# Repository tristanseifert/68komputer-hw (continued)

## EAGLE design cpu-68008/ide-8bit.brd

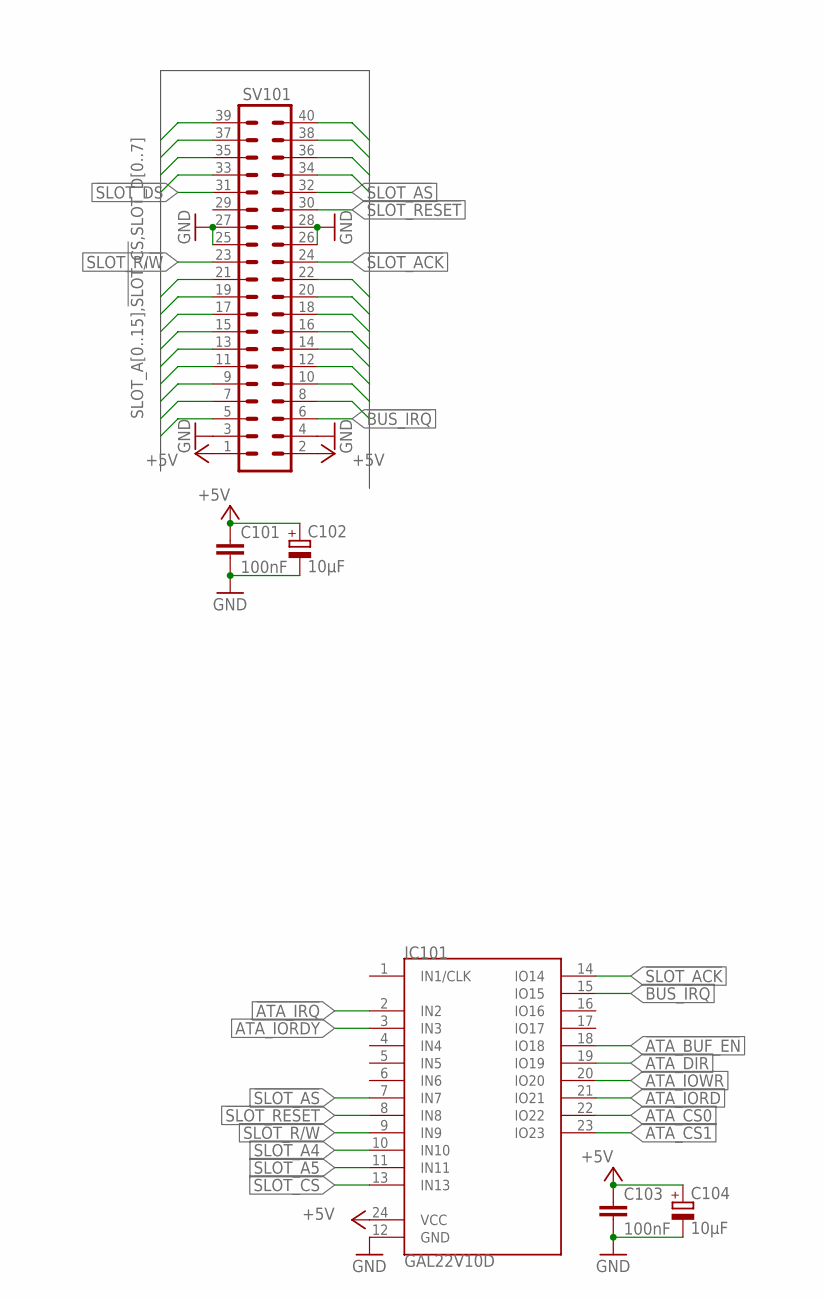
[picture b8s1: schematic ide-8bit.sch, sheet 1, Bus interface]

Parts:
C101, C103: 100nF; C0805; MOUSER 710-885012207072
C102, C104: 10µF; SMC_B; MOUSER 581-TAJB106K020RNJV
IC101: GAL22V10D; DIL24S; MOUSER_SOCKET 575-11044324
SV101: MA20-2W

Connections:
!ATA_BUF_EN: IC101.18 (IO18); also elsewhere on the board
!ATA_CS0: IC101.22 (IO22); also elsewhere on the board
!ATA_CS1: IC101.23 (IO23); also elsewhere on the board
!ATA_IRQ: IC101.2 (IN2); also elsewhere on the board
!BUS_IRQ: IC101.15 (IO15), SV101.6
!SLOT_ACK: IC101.14 (IO14), SV101.24
!SLOT_AS: IC101.7 (IN7), SV101.32
!SLOT_CS: IC101.13 (IN13), SV101.5
!SLOT_DS: SV101.31
!SLOT_RESET: IC101.8 (IN8), SV101.30
+5V: C101.1, C102.+, C103.1, C104.+, IC101.24 (VCC), SV101.1, SV101.2; also elsewhere on the board
ATA_DIR: IC101.19 (IO19); also elsewhere on the board
ATA_IORD: IC101.21 (IO21); also elsewhere on the board
ATA_IORDY: IC101.3 (IN3); also elsewhere on the board
ATA_IOWR: IC101.20 (IO20); also elsewhere on the board
GND: C101.2, C102.-, C103.2, C104.-, IC101.12 (GND), SV101.3, SV101.4, SV101.25, SV101.26, SV101.27, SV101.28; also elsewhere on the board
SLOT_A0: SV101.12; also elsewhere on the board
SLOT_A1: SV101.10; also elsewhere on the board
SLOT_A2: SV101.8; also elsewhere on the board
SLOT_A3: SV101.7
SLOT_A4: IC101.10 (IN10), SV101.9
SLOT_A5: IC101.11 (IN11), SV101.11
SLOT_A6: SV101.14
SLOT_A7: SV101.13
SLOT_A8: SV101.16
SLOT_A9: SV101.15
SLOT_A10: SV101.18
SLOT_A11: SV101.17
SLOT_A12: SV101.20
SLOT_A13: SV101.19
SLOT_A14: SV101.22
SLOT_A15: SV101.21
SLOT_D0: SV101.35; also elsewhere on the board
SLOT_D1: SV101.37; also elsewhere on the board
SLOT_D2: SV101.39; also elsewhere on the board
SLOT_D3: SV101.40; also elsewhere on the board
SLOT_D4: SV101.38; also elsewhere on the board
SLOT_D5: SV101.36; also elsewhere on the board
SLOT_D6: SV101.34; also elsewhere on the board
SLOT_D7: SV101.33; also elsewhere on the board
SLOT_R/!W!: IC101.9 (IN9), SV101.23

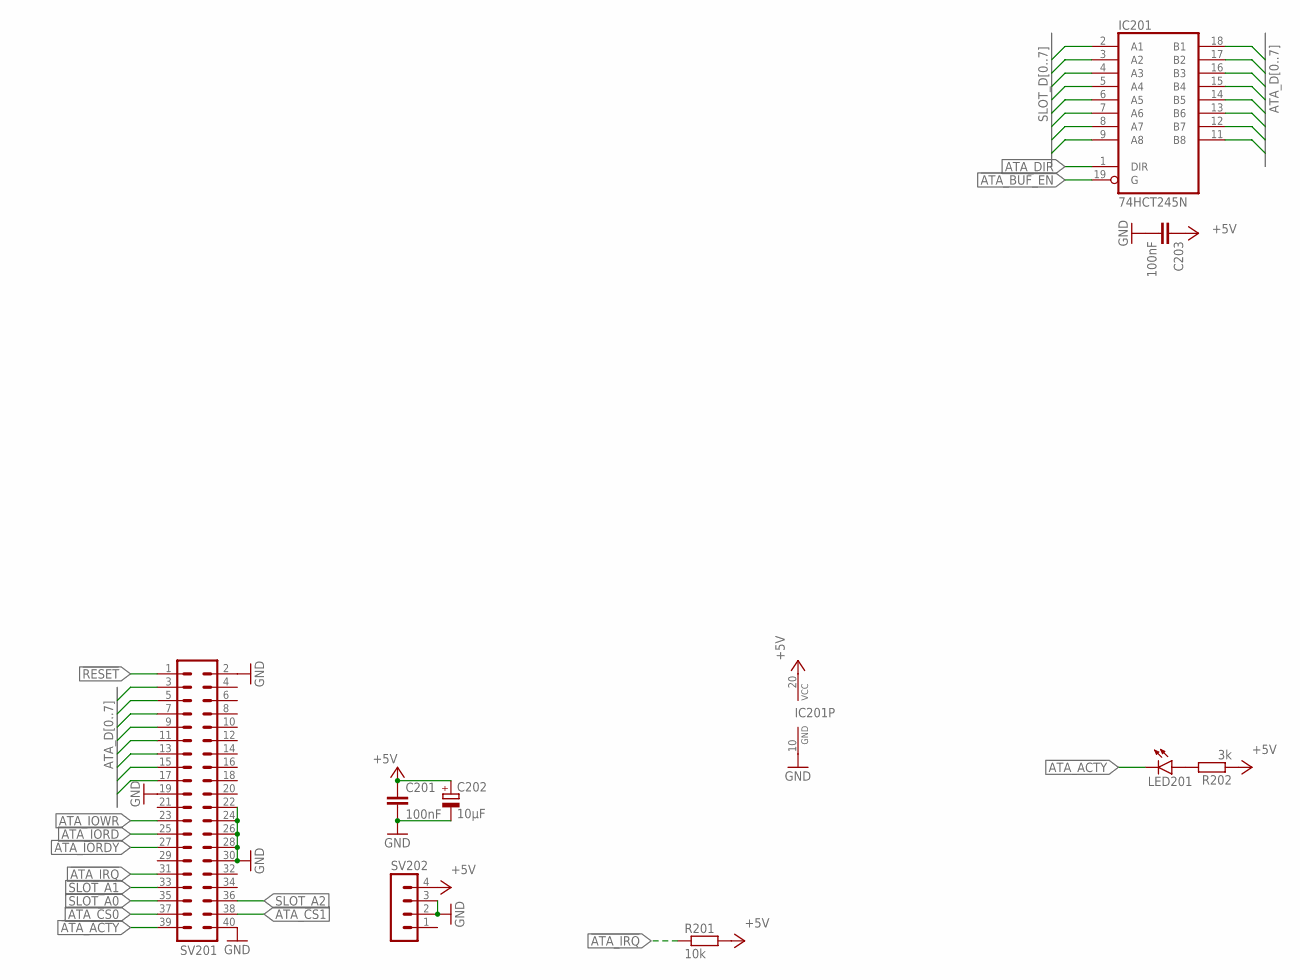
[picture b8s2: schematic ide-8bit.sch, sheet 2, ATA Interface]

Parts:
C201, C203: 100nF; C0805; MOUSER 710-885012207072
C202: 10µF; SMC_B; MOUSER 581-TAJB106K020RNJV
IC201: 74HCT245N; DIL20; MOUSER 595-SN74HCT245N
LED201: LEDCHIPLED_1206; CHIPLED_1206; MOUSER 710-156120VS75300
R201: 10k; R2012; MOUSER 652-CR0805FX-1002ELF
R202: 3k; R2012; MOUSER 652-CR0805JW-302ELF
SV201: ML40L
SV202: MA04-1

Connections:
!ATA_ACTY: LED201.C, SV201.39
!ATA_BUF_EN: IC201.19 (G); also elsewhere on the board
!ATA_CS0: SV201.37; also elsewhere on the board
!ATA_CS1: SV201.38; also elsewhere on the board
!ATA_IRQ: R201.1, SV201.31; also elsewhere on the board
!RESET: SV201.1
+5V: C201.1, C202.+, C203.1, IC201.20 (VCC), R201.2, R202.1, SV202.4; also elsewhere on the board
ATA_D0: IC201.18 (B1), SV201.17
ATA_D1: IC201.17 (B2), SV201.15
ATA_D2: IC201.16 (B3), SV201.13
ATA_D3: IC201.15 (B4), SV201.11
ATA_D4: IC201.14 (B5), SV201.9
ATA_D5: IC201.13 (B6), SV201.7
ATA_D6: IC201.12 (B7), SV201.5
ATA_D7: IC201.11 (B8), SV201.3
ATA_DIR: IC201.1 (DIR); also elsewhere on the board
ATA_IORD: SV201.25; also elsewhere on the board
ATA_IORDY: SV201.27; also elsewhere on the board
ATA_IOWR: SV201.23; also elsewhere on the board
GND: C201.2, C202.-, C203.2, IC201.10 (GND), SV201.2, SV201.19, SV201.22, SV201.24, SV201.26, SV201.28, SV201.30, SV201.40, SV202.2, SV202.3; also elsewhere on the board
unnamed: LED201.A, R202.2
SLOT_A0: SV201.35; also elsewhere on the board
SLOT_A1: SV201.33; also elsewhere on the board
SLOT_A2: SV201.36; also elsewhere on the board
SLOT_D0: IC201.2 (A1); also elsewhere on the board
SLOT_D1: IC201.3 (A2); also elsewhere on the board
SLOT_D2: IC201.4 (A3); also elsewhere on the board
SLOT_D3: IC201.5 (A4); also elsewhere on the board
SLOT_D4: IC201.6 (A5); also elsewhere on the board
SLOT_D5: IC201.7 (A6); also elsewhere on the board
SLOT_D6: IC201.8 (A7); also elsewhere on the board
SLOT_D7: IC201.9 (A8); also elsewhere on the board

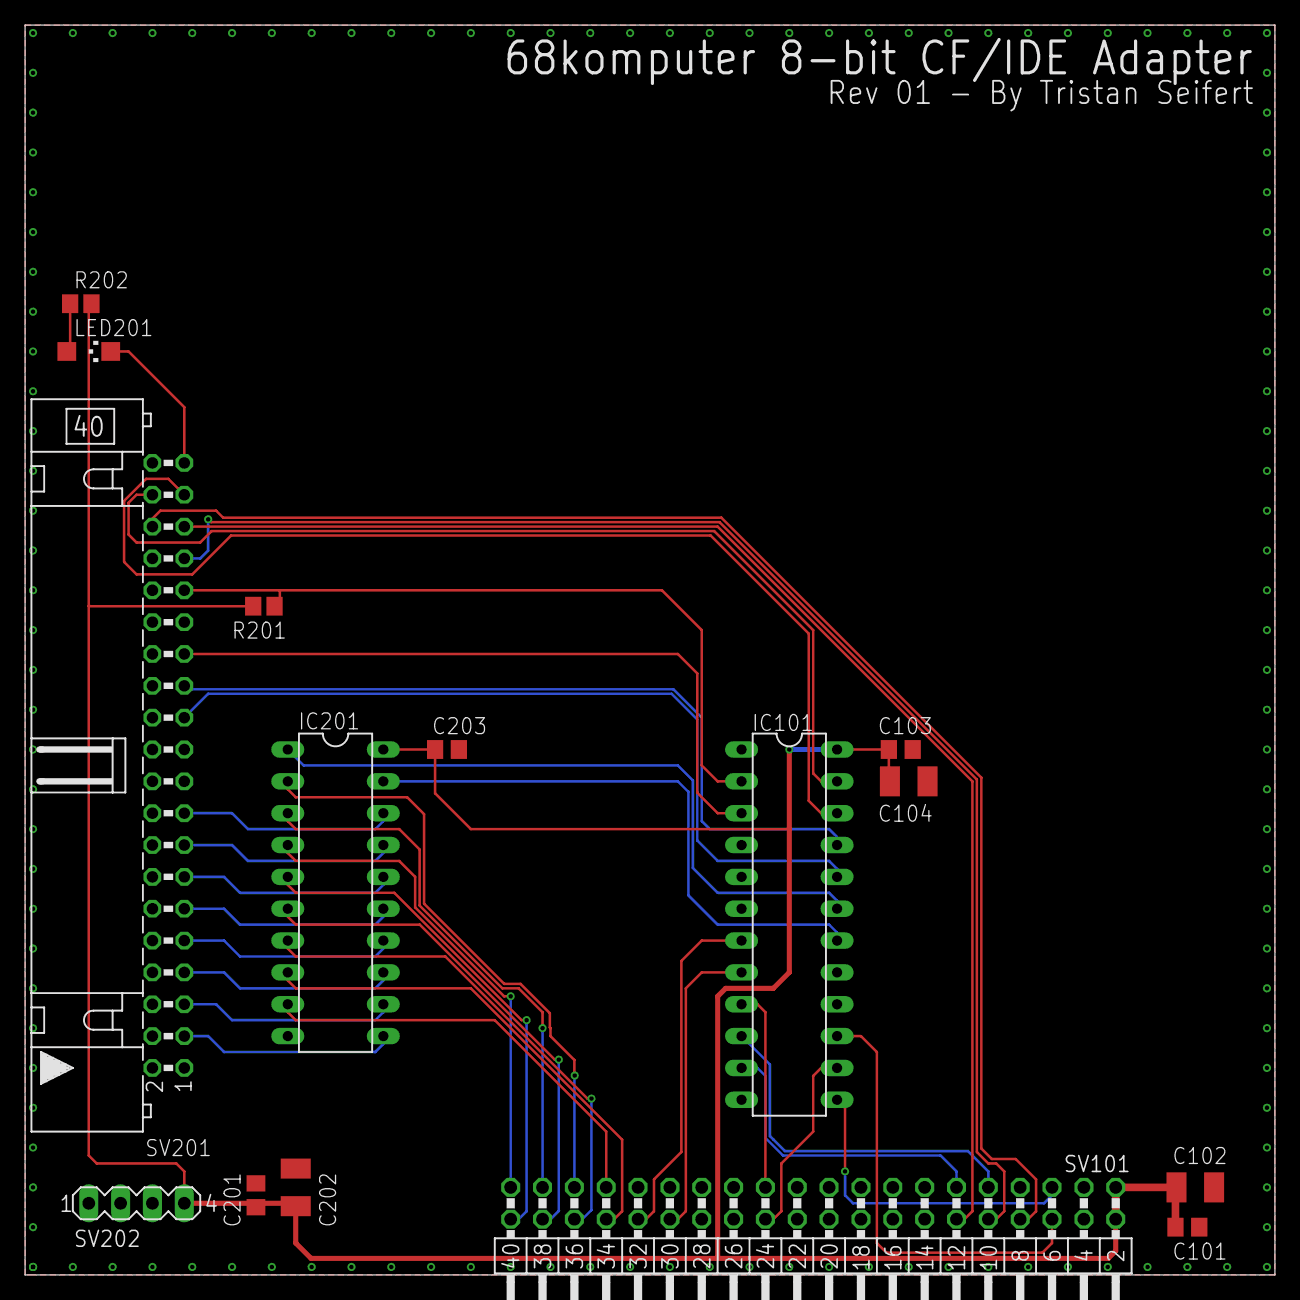
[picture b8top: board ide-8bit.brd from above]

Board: 2 copper layers, 99.7 x 99.7 mm, 15 parts (0 on the bottom side), 39 nets.

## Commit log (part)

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2018-12-04 add readme
2018-12-04 added psram to 68010 board
2018-12-04 added address decoding, interrupt handling, external bus interface
2018-12-07 added 68681 DUART
2018-12-07 routed address/data between banks of RAM/ROM
2018-12-08 added TIL311, DLx2416 LED displays
2018-12-10 added SIMM socket footprint
2018-12-12 routed more signals, added power connector
2019-09-28 more stuff got routed for 68008
2019-09-29 routed duart IO and serial channels
2019-09-30 finish routng
2019-10-06 replaced CPLD with PLDs
2019-10-08 added uart/rs232 adapter
2019-10-13 rev 01 boards for cpu-68008 sent to fab
2019-10-25 preliminary expansion backplane for 68komputer-008
2019-10-27 finished routing backplane
2019-10-28 start work on sound board
2019-10-29 start working on adding midi in/out to sound board
2019-10-31 finished midi circuit frontends
2019-11-04 Added 8-bit IDE board Finished routing of sound board
2019-11-06 finished schematic for tms9918 board, started routing
2019-11-15 basic 68000 based computer
2019-11-16 Finished routing expansion connector for 68000 board
2019-11-17 Started working on 2MB RAM expansion board for 68000 CPU
2019-11-18 2MB RAM Expansion: - Finished routing all signals
2019-11-21 IO board: - Added 82C55 PIO
    RAM board:
    - Tweaked tolerances between some traces
    - Fixed naming of parts
2020-02-11 Started work on sound board
2021-10-28 moved old files
2021-11-04 added memory, peripherals
2021-11-11 Peripherals and general connection stuff
2021-11-12 More backplane stuff; added footprints for most
2021-11-13 Placed most items on pcb
    - Laid out most components where they should go on the board; mostly
    routed the connector side of the bus buffers and the address bus
    - Added 3d models for PLCC sockets, RTC clock module
2021-11-14 More control signals; start RAM routing
    - Started routing the address/data bus for the RAM, including some
    rejigging of the data bus layout
    - Added a fuse and power conditioning for 12V, to be used for the analog
    section on the sound side
2021-11-15 Start peripheral routing
    - Begin routing some of the peripheral section, particularly the NVRAM
    is fully connected (sans chip select) now
    - Added an I2C EEPROM (with serial number) on board the CPU card for
    automatic identification
    - Minor cleanups and space squishing of the board. There may in fact be
    sufficient space to still fit a boot ROM (likely a surface mount
2021-11-16 Completed board routing
    - Finished routing all of the signals on the board :D it still needs a
    check over to make sure it's not fucked though
    - Split sound stuff into its own sheet
2021-11-17 Added memory access type signal
    - Since function codes aren't provided on the backplane, we instead have
    a signal that's driven low to indicate that the access is to memory
    rather than some other type (CPU space). It's open drain with a 10k
    pullup, which is _hopefully_ sufficient.
2021-11-19 Begin work on blinkenlights board
    - This is a simple board with pretty TIL311 displays for the
    address/data busses, lots of blinking lights, and sockets for boot
    ROMs for testing. It connects directly to the CPU board through a
    female right angle DIN41612 connector.
    - Added footprints for Deltron 571-0x00 test sockets
2021-11-30 Tweaks to IOs on 68k board
    - Added an I2C IRQ line, so that I2C peripherals can request servicing.
    This is mostly used for the control panel/backplane management
    functions.
2021-12-01 Switched one of the RAMs for a flash chip
    - This should allow us to have a boot ROM on the board; it will need to
    be bootstraped and programmed in-system by some external jig though.
2021-12-01 Added high byte flash chip
    - Replaced one of the RAMs with another flash, so that we can have
    on-board boot ROM of 1M. It'll have to be programmed in system (or
    very flimsily out of system before soldering) so a switch to remap the
    flash to elsehwere in the address space is provided (formerly BERR
    inhibit switch)
2021-12-01 Added ROM sockets to blinkenlights
    - Also started routing some of the IOs and powers for the displays
2021-12-03 did some things
2021-12-05 Added ATSAM4 CPU to blinkenlights
    - This big ol ARM chip is gonna be hooked up to the 68k bus, so that we
    can do bus transactions and (slowly) single step the physical machine.
    This will make bringup simpler and allow programming of the flash
    chips on the CPU board.
    - Added a footprint for an USB-C connector (lol)
2021-12-06 Routed address/data bus on blinkenlights
    - It goes to the funky hex display bois now and is routed so that it
    should be pretty ez to yeet on down into level shifters for the big
    ARM chip that runs the show
2021-12-07 Connected data/address bus to expanders
    - Finished routing the remaining address and data lines to the SPI IO
    expanders, which are used externally to control the bus. Also removed
    some superfluous level shifters
2021-12-08 Mostly finished blinkenlights contraption
    - Added some headers that can have logic probes connected to them; we
    need to route them and ensure the pins are correct
2021-12-09 Expose CPU function code on backplane
    - Routed the function code signals to the backplane; they're pulled to
    ground so that if a bus mastering device doesn't drive them the world
    won't explode (it will be a supervisor data access)
2021-12-09 Added a few more test points
    - Also, tweaked the package of the I2C translator to be one that's
    actually in stock
2021-12-11 Minor cleanup of CPU board
    - Switched out of stock 2 bit level shifters for 8 bit part we already
    have; this means that the function codes will be buffered along with
    all other signals.
2021-12-12 Replaced many B case caps with A case
    - There were sufficiently many 5V tantalum capcaitors on the
    blinkenlights board with the B case footprint (for 25V) rather than
    the A case (for 16V) assigned.
2021-12-14 Added logic equations for CPU board
    - These are the equations that get programmed into the GALs that
    actually drive the control signals and so forth.
    - Minor cleanups to the CPU board
2021-12-16 More minor tweaks to CPU board
    - Added an I2C expansion header, which some GPIO stuff could be
    connected to for testing, and to probe the on-board I2C bus with an
    external logic analyzer.
    - The parts on it are frozen at this point since they have been ordered
2021-12-16 Added gerbers sent to manufacturing (Rev 01)
2021-12-30 Minor fixes for wrong parts
    - Mostly an incorrect fuse value and the wrong type of buffer on the CPU
    board buttons
2021-12-31 Finished routing new address/data from backplane
    - Routed the traces for the address/data bus from the connector and
    along the memories that need them. The NVRAM is fully connected to the
    bus, along with the peripheral section.
    We'll need to assign address lines to the SRAMs, then connect the
    flash chips next.
2022-01-02 More footprints and symbols
    - Created footprints/symbols for a few power regulation components for
    the backplane management board
2022-01-02 Routed backplane mgmt board
    - Finished routing of the complete backplane management board; it
    doesn't do much other than provide power (with monitoring) and an
    audio output (with volume control) from the backplane.
    Originally this was gonna have a display but there's no space on the
    front panel for that.
2022-01-04 More backplane work
    - Added pull up/down resistors at end of board to bring the various
    data/address lines to a controlled state, rather than floating, and
    attempt to control reflections
    - Added a clock buffer so each slot gets its own nice buffered clock.
    The clock buffer used is only 1:5 fanout, so the last two slots share
    a clock line.
2022-01-05 More optimization of backplane
    - Fixed a few DRC errors and added LEDs with the spare IOs on the I2C
    expander.
2022-01-08 Start work on a relay output board
    - This is a super simple test peripheral board, just a latch and a bunch
    of relays for clicky sounds. It serves as a test of the backplane and
    I2C based detection/address allocation mechanisms.
2022-01-08 Function codes, /DTACK for relay board
    - Consider the state of the function code signals (so we don't decode
    CPU space cycles as accesses) and assert /DTACK when the latch signal
    is asserted. This should work for bus speeds of up to around 16MHz
2022-01-10 Minor tweaks to all boards
    - Moved around some traces on the 68000 CPU card for prettiness
    - Added a connector on the backplane to provide +5V/+12V without a
    management card installed (for testing)
2022-01-12 Tweaks to CPU board layout
    - Made some more space around the ROM sockets, in hopes of maybe fitting
    spicier sockets than standard machine pin sockets. There's the Aries
    Electronics EJECT-A-DIP sockets that might fit now.
2022-01-14 Minor tweaks to power board
    - Reorganized the layout of input protection to accomodate a different
    (cheaper) input connector; also added some better thermal dissipation
    for the protection MOSFETs.
2022-01-14 Removed GAL from relay board
    - Replaced the GAL on the relay board with some hard 74-series logic;
    this means the board needs zero "hard to get" parts.
    All the address decoding is done by a '688 magnitude comparison IC,
    which is LS logic so this board needs to consist of HCT logic to deal
    with its lower active high level.
    - Replaced 3D model for the hexadecimal rotary switches to one that has
2022-01-24 Added +12V regulator to backplane mgmt
    - Added the components for a discrete switching regulator (that is, with
    external switching MOSFETs, but a fancy little switching controller)
    to generate the 12V rail, at up to 10A. This is then further regulated
    to provide 5V for the board itself, and for the rest of the system.
2022-02-03 Minor layout tweaks across the board
    - Added an input for a test clock, and a jumper for sending this clock
    instead of the CPU clock to the clock pins of the expansion cards on
    the backplane boards
    - Reworked a bunch of the power supply board
    - Minor changes (to consolidate BOMs) on CPU board for some capacitors,
    they were replaced with SMD versions
2022-02-05 Finished backplane breakout
    - All of the backplane signals (for an expansion card) are brought out
    to 2x10 headers, which can connect to the logic analyzer through
    isolation adapters or direct probing in a more compact pinout
    - Added a footprint for a shrouded 2x10 header
2022-03-02 Added backplane GAL equations
